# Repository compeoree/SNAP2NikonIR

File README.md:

# SNAP2NikonIR
A full project (mechanical, electrical, software) clone/upgrade of the Nikon ML-L3 IR remote.

It functions in two ways:
1) Simple ML-L3 clone - press the button to trigger the shutter
2) A SNAP to IR interface

SNAP is a method to capture photos using a compatible camera and certain astromony mounts/hardware. It is typically wired, which Nikon cameras do not support. This device will convert the SNAP standard 2.5mm audio TRS connector to an IR signal.

A battery is required and the selected CR1632 should last around 18 months.

OshPark PCB
https://oshpark.com/shared_projects/UpTNsuQq

Fusion 360 CAD
https://a360.co/35Rz2Ta

Sources:
* https://www.sbprojects.net/projects/nikon/
* http://www.bigmike.it/ircontrol/
* http://allynh.com/blog/making-an-ir-remote-control-for-a-nikon-camera/
* https://www.christidis.info/index.php/personal-projects/arduino-nikon-infrared-command-code
* https://www.doc-diy.net/photo/remote_pinout/canon_pinout.png

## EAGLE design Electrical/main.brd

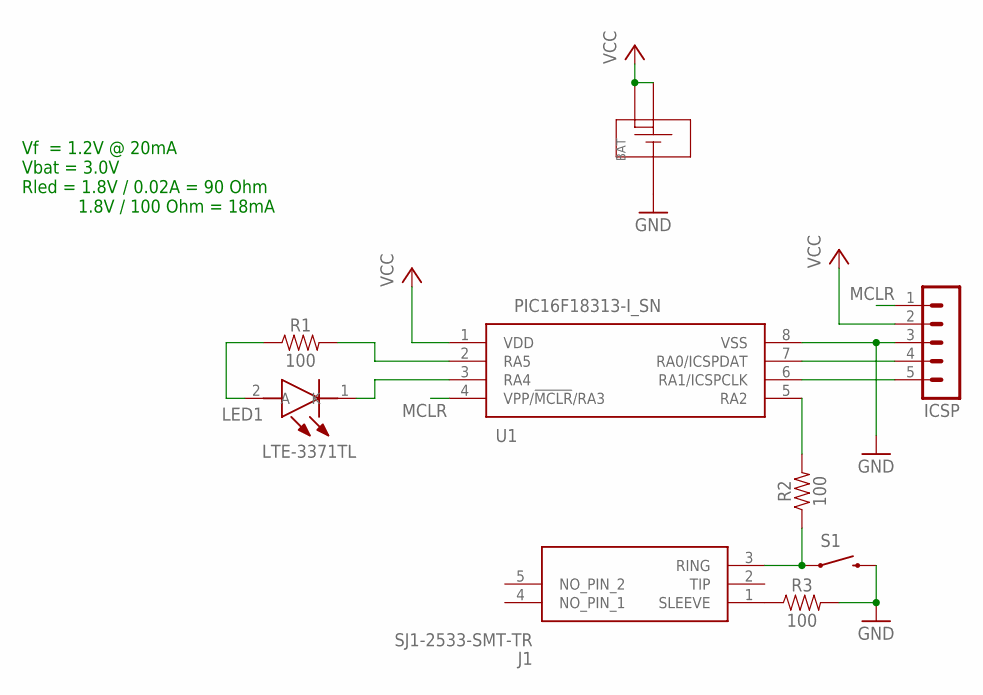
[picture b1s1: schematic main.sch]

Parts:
BAT: SMTM1632
ICSP: MA05-1
J1: SJ1-2533-SMT-TR; SJ12533SMTTR
LED1: LTE-3371TL; LTE3371TL
R1, R2, R3: 100; 0603
S1: SWITCH-MOMENTARY-2PTH; TACTILE-PTH
U1: PIC16F18313-I_SN; SOIC127P600X175-8N

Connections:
GND: BAT.1 (-), ICSP.3, R3.2, S1.3 (2), U1.8 (VSS)
MCLR: ICSP.1, U1.4 (VPP/!MCLR!/RA3)
unnamed: R1.2, U1.2 (RA5)
unnamed: ICSP.4, U1.7 (RA0/ICSPDAT)
unnamed: ICSP.5, U1.6 (RA1/ICSPCLK)
unnamed: LED1.1 (K), U1.3 (RA4)
unnamed: LED1.2 (A), R1.1
unnamed: J1.1 (SLEEVE), R3.1
unnamed: J1.3 (RING), R2.1, S1.1
unnamed: R2.2, U1.5 (RA2)
VCC: BAT.2 (+), BAT.3 (+), ICSP.2, U1.1 (VDD)

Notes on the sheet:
Vf = 1.2V @ 20mA Vbat = 3.0V Rled = 1.8V / 0.02A = 90 Ohm 1.8V / 100 Ohm = 18mA

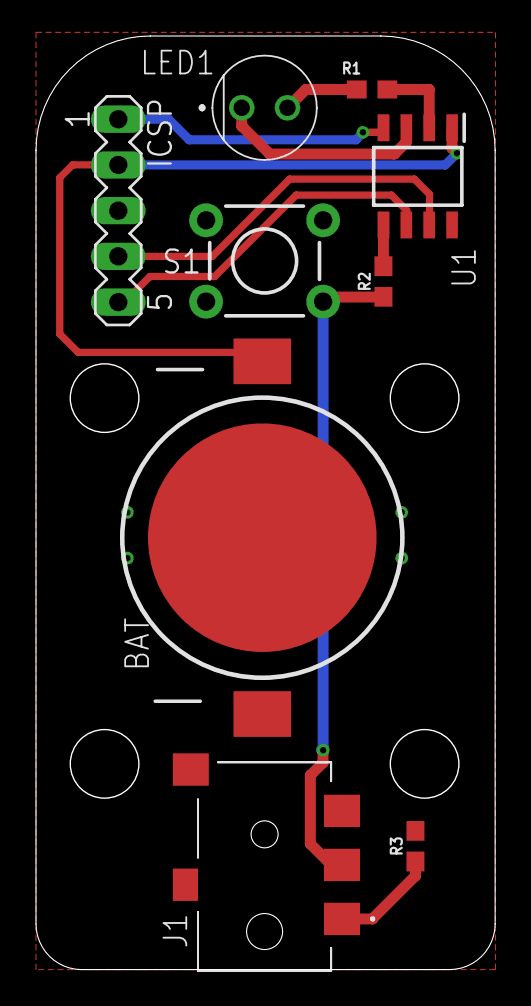
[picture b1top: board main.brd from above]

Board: 2 copper layers, 25.5 x 51.9 mm, 9 parts (0 on the bottom side), 11 nets.

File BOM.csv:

"Qty";"Value";"Device";"Package";"Parts";"Description";"DESCRIPTION";"HEIGHT";"MANUFACTURER_NAME";"MANUFACTURER_PART_NUMBER";"MF";"MOUSER_PART_NUMBER";"MOUSER_PRICE-STOCK";"MPN";"OC_FARNELL";"OC_NEWARK";"POPULARITY";"PROD_ID";"VALUE";
"1";"";"MA05-1";"MA05-1";"ICSP";"PIN HEADER";"";"";"";"";"";"";"";"";"unknown";"unknown";"29";"";"";
"3";"100";"100OHM-0603-1/10W-1%";"0603";"R1, R2, R3";"100Ω resistor";"";"";"";"";"";"";"";"";"";"";"";"RES-07863";"100";
"1";"LTE-3371TL";"LTE-3371TL";"LTE3371TL";"LED1";"Infrared Emitters Infrared 940nm 1.25V, 20mA, 140deg";"Infrared Emitters Infrared 940nm 1.25V, 20mA, 140deg";"8.85mm";"Lite-On";"LTE-3371TL";"";"859-LTE-3371TL";"https://www.mouser.com/Search/Refine.aspx?Keyword=859-LTE-3371TL";"";"";"";"";"";"";
"1";"PIC16F18313-I_SN";"PIC16F18313-I_SN";"SOIC127P600X175-8N";"U1";"8-bit Microcontrollers - MCU 8-Bit MCU 3.5K Flash 256 RAM 256 EEPROM";"8-bit Microcontrollers - MCU 8-Bit MCU 3.5K Flash 256 RAM 256 EEPROM";"1.75mm";"Microchip";"PIC16F18313-I/SN";"";"579-PIC16F18313-I/SN";"https://www.mouser.co.uk/ProductDetail/Microchip-Technology/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";"";"";"";"";"";"";
"1";"SJ1-2533-SMT-TR";"SJ1-2533-SMT-TR";"SJ12533SMTTR";"J1";"Phone Connectors Audio Jacks";"Phone Connectors Audio Jacks";"3.1mm";"CUI Devices";"SJ1-2533-SMT-TR";"";"490-SJ1-2533-SMT-TR";"https://www.mouser.co.uk/ProductDetail/CUI-Devices/SJ1-2533-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";"";"";"";"";"";"";
"1";"SMTM1632";"SMTM1632";"SMTM1632";"BAT";"16mm Coin Cell Battery Holder";"";"";"";"";"";"";"";"";"";"";"";"";"";
"1";"SWITCH-MOMENTARY-2PTH";"SWITCH-MOMENTARY-2PTH";"TACTILE-PTH";"S1";"Various NO switches- pushbuttons, reed, etc";"";"";"";"";"";"";"";"";"";"";"";"";"";

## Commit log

2020-11-01 Added datasheets
2020-11-01 Added schematic and PCB
2020-11-01 Added bill of materials
2020-11-01 Added firmware
2020-11-01 Added useful compile output: memory usage and inline disassembly
2020-11-01 Ignore intermediate build files and private folders
2020-11-01 Converted to Mouser BOM and added PCB vendor
2020-11-01 Added mechanical files
2020-11-01 Added STL files
2020-11-01 Updated sources
2020-11-01 Fixed formatting on sources

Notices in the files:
Electrical/main.brd:
©2020 L.McCarthy
parts and their libraries:
SparkFun-Resistors: Licensing: Creative Commons ShareAlike 4.0 International - https://creativecommons.org/licenses/by-sa/4.0
